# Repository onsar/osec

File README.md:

# osec
###Proyecto de para el desarrollo de un demostrador de software libre para el control de la energía

En la primera fase monitorizamos una instalación solar fotovoltaica mixta que esta compuesta por paneles fotovoltaicos y térmicos. Los tipos de sensores que incluye son:

* Intensidad en continua
* Temperatura del agua
* Caudal
* Presión del circuito hidráulico

En una segunda fases optimizaremos el circuito

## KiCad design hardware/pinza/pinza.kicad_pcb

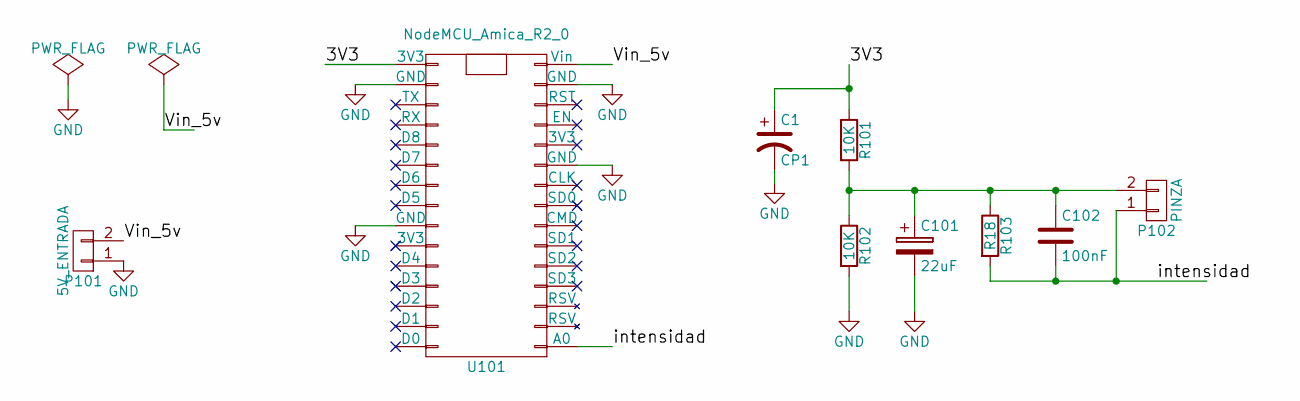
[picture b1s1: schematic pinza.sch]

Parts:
C1: CP1; C_Radial_D5_L11_P2
C101: 22uF; C_Radial_D5_L11_P2
C102: 100nF; C_Disc_D3_P2.5
P101: 5V_ENTRADA; bornier2
P102: PINZA; bornier2
R101, R102: 10K; Resistor_Horizontal_RM10mm
R103: R18; Resistor_Horizontal_RM10mm
U101: NodeMCU_Amica_R2_0; NodeMCU_Amica_R2

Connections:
/3V3: C1.1, R101.1, U101.16 (3V3)
/Vin_5v: P101.2, U101.15 (Vin)
/intensidad: C102.2, P102.1, R103.2, U101.1 (A0)
GND: C1.2, C101.2, P101.1, R102.2, U101.10 (GND), U101.14 (GND), U101.17 (GND), U101.24 (GND)
unnamed: C101.1, C102.1, P102.2, R101.2, R102.1, R103.1

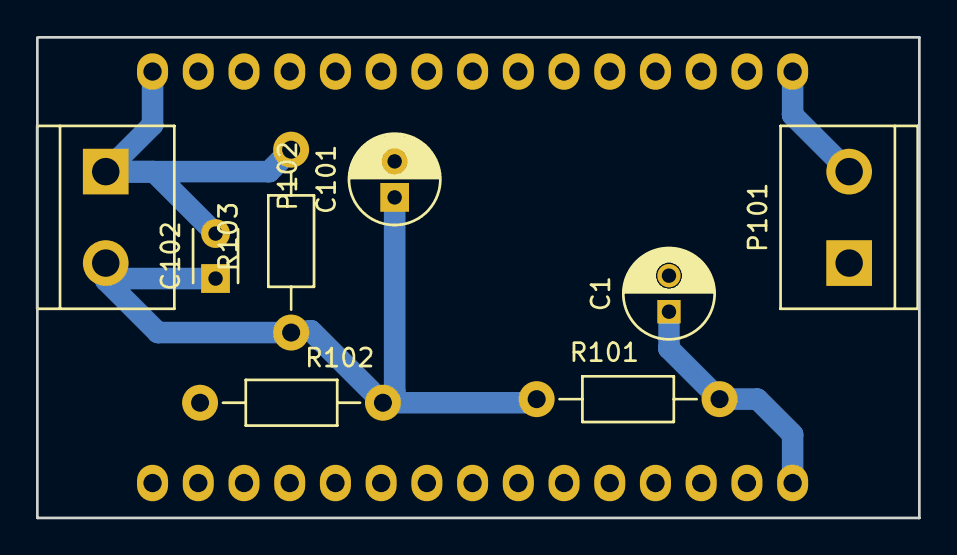
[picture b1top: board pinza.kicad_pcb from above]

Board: 2 copper layers, 49.0 x 26.7 mm, 9 parts (1 on the bottom side), 5 nets.

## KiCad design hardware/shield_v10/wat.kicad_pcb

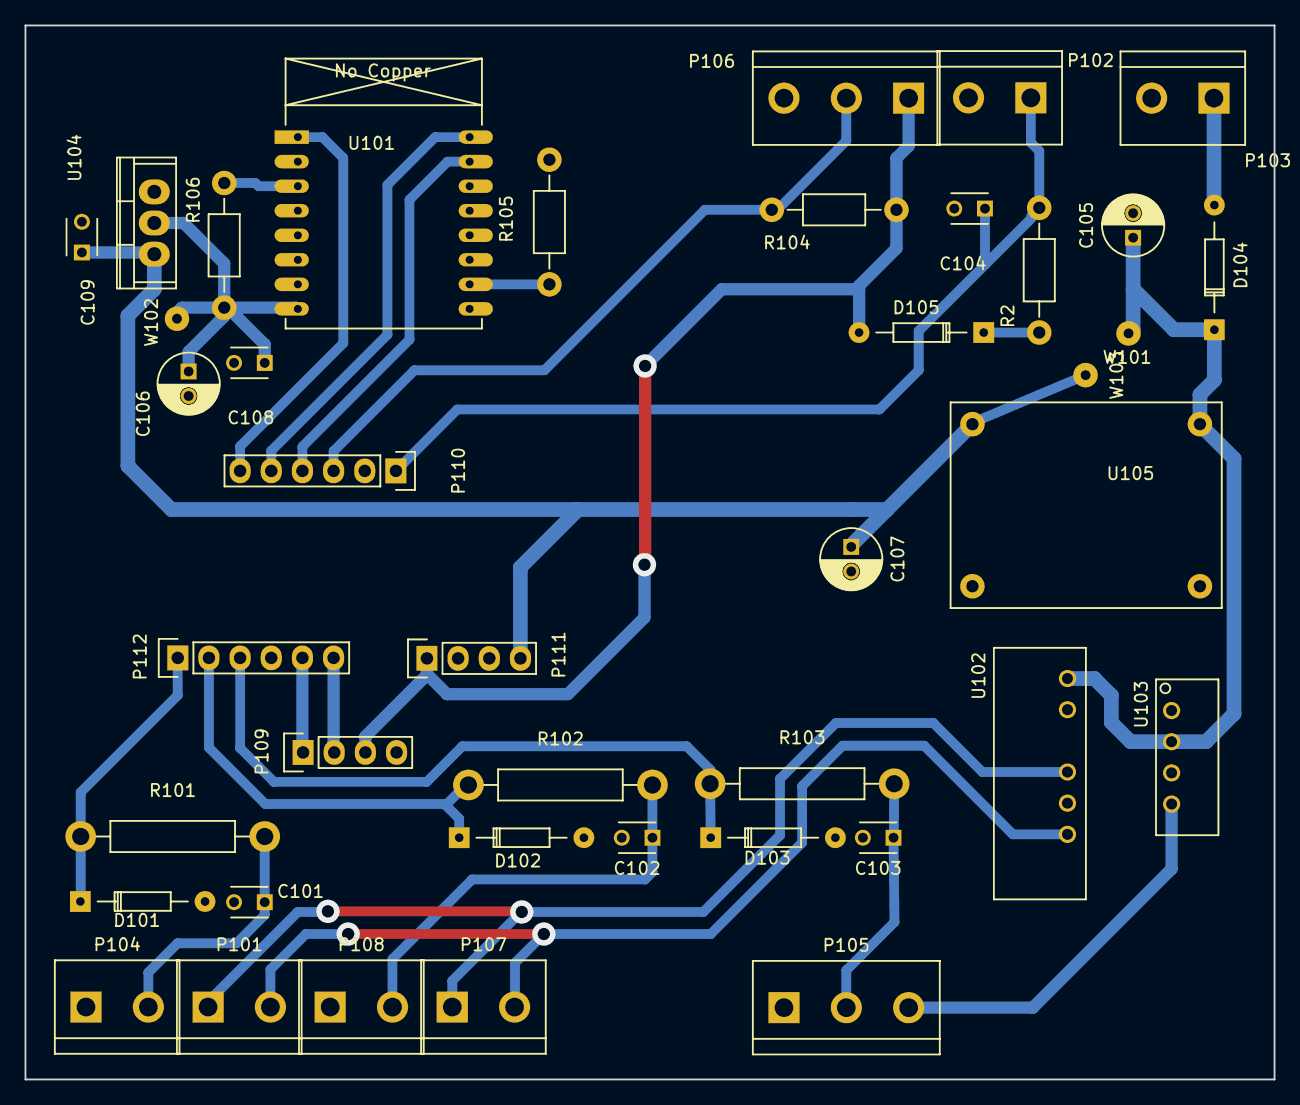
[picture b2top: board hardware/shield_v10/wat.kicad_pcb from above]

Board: 2 copper layers, 101.8 x 85.9 mm, 41 parts (0 on the bottom side), 25 nets.

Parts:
C101, C102, C103, C104, C108, C109: 100nF; C_Disc_D3_P2.5
C105: 220uF; C_Radial_D5_L11_P2
C106, C107: 22uF; C_Radial_D5_L11_P2
D101, D102, D103: ZENER; Diode_DO-35_SOD27_Horizontal_RM10
D104, D105: 1N4007; Diode_DO-35_SOD27_Horizontal_RM10
P101: INTEN_1_V; bornier2
P102: CAUDAL_1; bornier2
P103: V_IN; bornier2
P104: INTEN_1_I; bornier2
P105: PRESION_1; bornier3
P106: 18b20; bornier3
P107: INTEN_2_V; bornier2
P108: INTEN_2_I; bornier2
P109: LCD_I2C; Pin_Header_Straight_1x04
P110: ARD_DI_06; Pin_Header_Straight_1x06
P111: ARD_ALI_04; Pin_Header_Straight_1x04
P112: ARD_AN_I2C; Pin_Header_Straight_1x06
R2, R105, R106: 10K; Resistor_Horizontal_RM10mm
R101, R102, R103: 1K; Resistor_RM15mm_pad
R104: 2K; Resistor_Horizontal_RM10mm
U101: ESP-12; ESP-07v2_pad
U102: Recom-rd
U103: RO-1224S; RO-xxxxS
U104: LM1117; TO-220-LM117
U105: mp-1584; MP-1584-SD
W101: +12V; SolderWirePad_single_0-8mmDrill
W102: +3,3V; SolderWirePad_single_0-8mmDrill
W103: +8V; SolderWirePad_single_0-8mmDrill

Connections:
/18b20: P106.2, P110.3, R104.1
/+15_voltios: P101.2, P107.2, U102.6
/+24_voltios: P105.3, U103.4
/-15_voltios: P101.1, P107.1, U102.4
/Var_8V: C107.1, C109.1, P111.4, U104.VI, U105.3, W103.1
/Ves_3V3: C106.1, C108.1, R106.1, U101.8, U104.VO, W102.1
/Vin_12V: C105.1, D104.1, U102.1, U103.2, U105.2, W101.1
/Vpc_5V: D105.2, P106.1, P109.3, P111.1, R104.2
/caudal_1: C104.1, P102.1, P110.1, R2.2
/e_cpd: R106.2, U101.3
/e_g15: R105.1, U101.10
/e_rst: P110.6, U101.1
/e_rx: P110.4, U101.15
/e_tx: P110.5, U101.16
/intensidad_1: D101.1, P112.1, R101.1
/intensidad_2: D102.1, P112.2, R102.1
/presion_1: D103.1, P112.3, R103.1
/scl: P109.2, P112.6
/sda: P109.1, P112.5
GND: C101.2, C102.2, C103.2, C104.2, C105.2, C106.2, C107.2, C108.2, C109.2, D101.2, D102.2, D103.2, P102.2, P103.2, P104.1, P105.1, P106.3, P108.1, P109.4, P111.3, R105.2, U101.9, U102.2, U102.5, U103.1, U103.3, U104.GND, U105.1, U105.4
unnamed: C101.1, P104.2, R101.2
unnamed: C102.1, P108.2, R102.2
unnamed: C103.1, P105.2, R103.2
unnamed: D104.2, P103.1
unnamed: D105.1, R2.1

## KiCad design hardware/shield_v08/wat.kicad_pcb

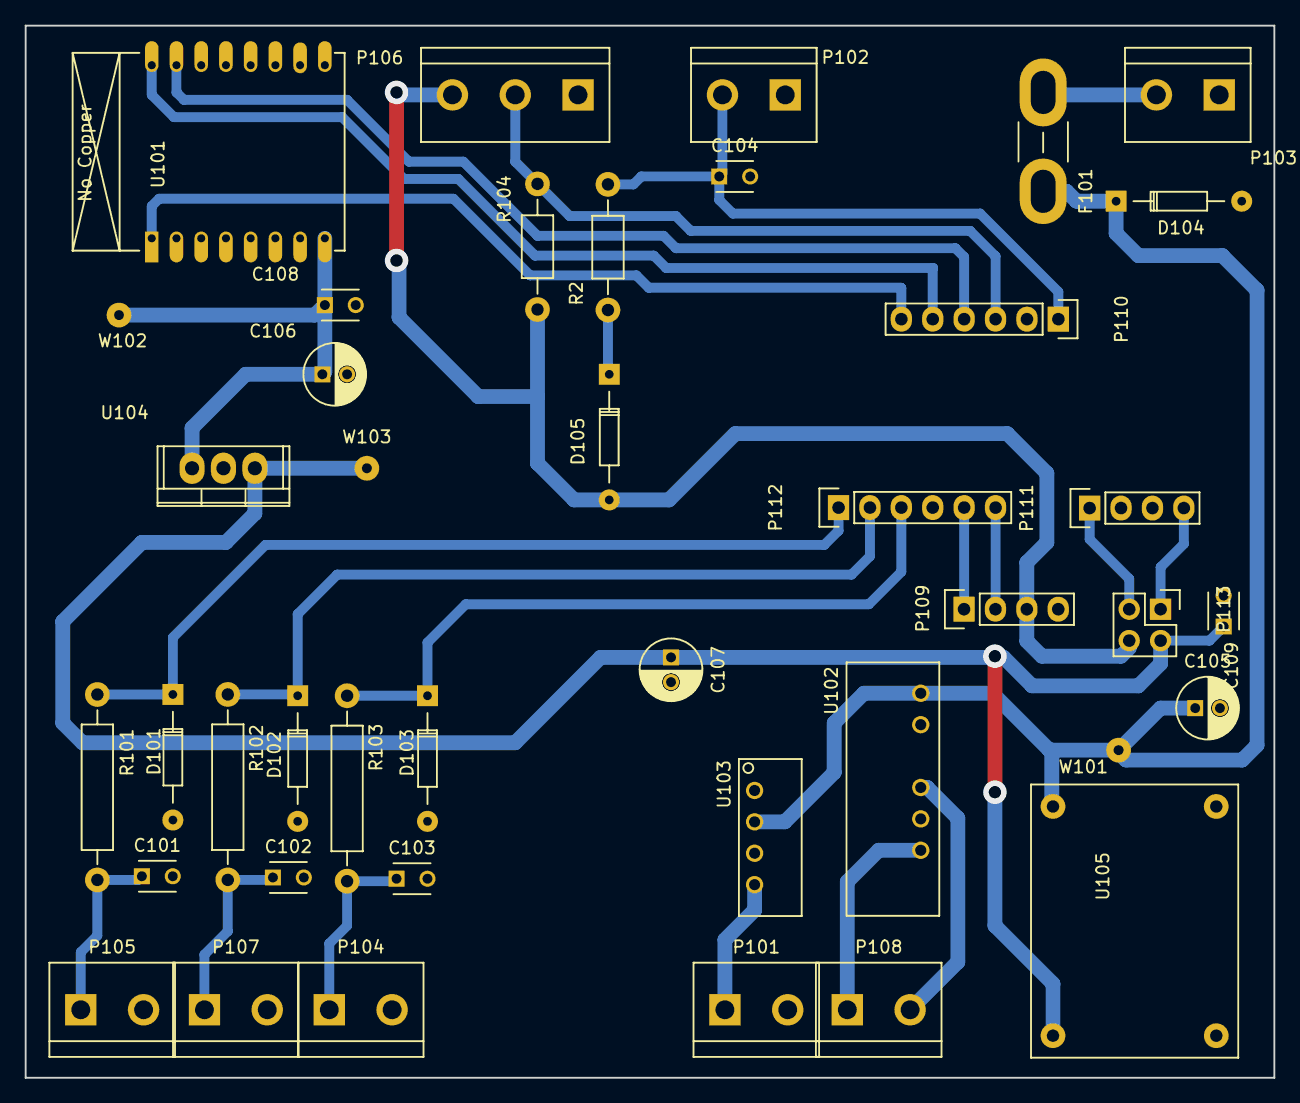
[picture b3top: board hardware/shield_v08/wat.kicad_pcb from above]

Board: 2 copper layers, 101.0 x 85.1 mm, 41 parts (0 on the bottom side), 25 nets.

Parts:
C101, C102, C103, C104, C108, C109: 100nF; C_Disc_D3_P2.5
C105: 220uF; C_Radial_D5_L11_P2
C106, C107: 22uF; C_Radial_D5_L11_P2
D101, D102, D103: ZENER; Diode_DO-35_SOD27_Horizontal_RM10
D104, D105: 1N4007; Diode_DO-35_SOD27_Horizontal_RM10
F101: Fuse; BladeFuse-Mini
P101: 24VOL; bornier2
P102: CAUDAL_1; bornier2
P103: V_IN; bornier2
P104: PRESION_1; bornier2
P105: INTENSIDAD_1; bornier2
P106: 18b20; bornier3
P107: INTENSIDAD_2; bornier2
P108: 15VOL; bornier2
P109: LCD_I2C; Pin_Header_Straight_1x04
P110: ARD_DI_06; Pin_Header_Straight_1x06
P111: ARD_ALI_04; Pin_Header_Straight_1x04
P112: ARD_AN_I2C; Pin_Header_Straight_1x06
P113: CONN_02X02; Pin_Header_Straight_2x02
R2: 10K; Resistor_Horizontal_RM10mm
R101, R102, R103: 1K; Resistor_Horizontal_RM15mm
R104: 2K; Resistor_Horizontal_RM10mm
U101: ESP-12; ESP-07v2
U102: Recom-rd
U103: RO-1224S; RO-xxxxS
U104: LM1117; TO-220
U105: mp-1584; MP-1584-SD
W101: +12V; SolderWirePad_single_0-8mmDrill
W102: +3,3V; SolderWirePad_single_0-8mmDrill
W103: +8V; SolderWirePad_single_0-8mmDrill

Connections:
/18b20: P106.2, P110.3, R104.1
/Var_8V: C107.1, C109.1, P113.2, U104.VI, U105.3, W103.1
/Ves_3V3: C106.1, C108.1, U101.8, U104.VO, W102.1
/Vin_12V: C105.1, D104.1, F101.2, U102.1, U103.2, U105.2, W101.1
/Vpc_5V: D105.2, P106.3, P109.3, P113.4, R104.2
/caudal_1: C104.1, P102.2, P110.1, R2.2
/e_rst: P110.6, U101.1
/e_rx: P110.4, U101.15
/e_tx: P110.5, U101.16
/intensidad_1: D101.1, P112.1, R101.1
/intensidad_2: D102.1, P112.2, R102.1
/presion_1: D103.1, P112.3, R103.1
/scl: P109.2, P112.6
/sda: P109.1, P112.5
GND: C101.2, C102.2, C103.2, C104.2, C105.2, C106.2, C107.2, C108.2, C109.2, D101.2, D102.2, D103.2, D104.2, P101.2, P102.1, P103.1, P104.2, P105.2, P106.1, P107.2, P109.4, P111.3, U101.9, U102.2, U102.5, U103.1, U103.3, U104.GND, U105.1, U105.4
unnamed: C101.1, P105.1, R101.2
unnamed: C102.1, P107.1, R102.2
unnamed: C103.1, P104.1, R103.2
unnamed: D105.1, R2.1
unnamed: F101.1, P103.2
unnamed: P101.1, U103.4
unnamed: P108.1, U102.6
unnamed: P108.2, U102.4
unnamed: P111.1, P113.3
unnamed: P111.4, P113.1

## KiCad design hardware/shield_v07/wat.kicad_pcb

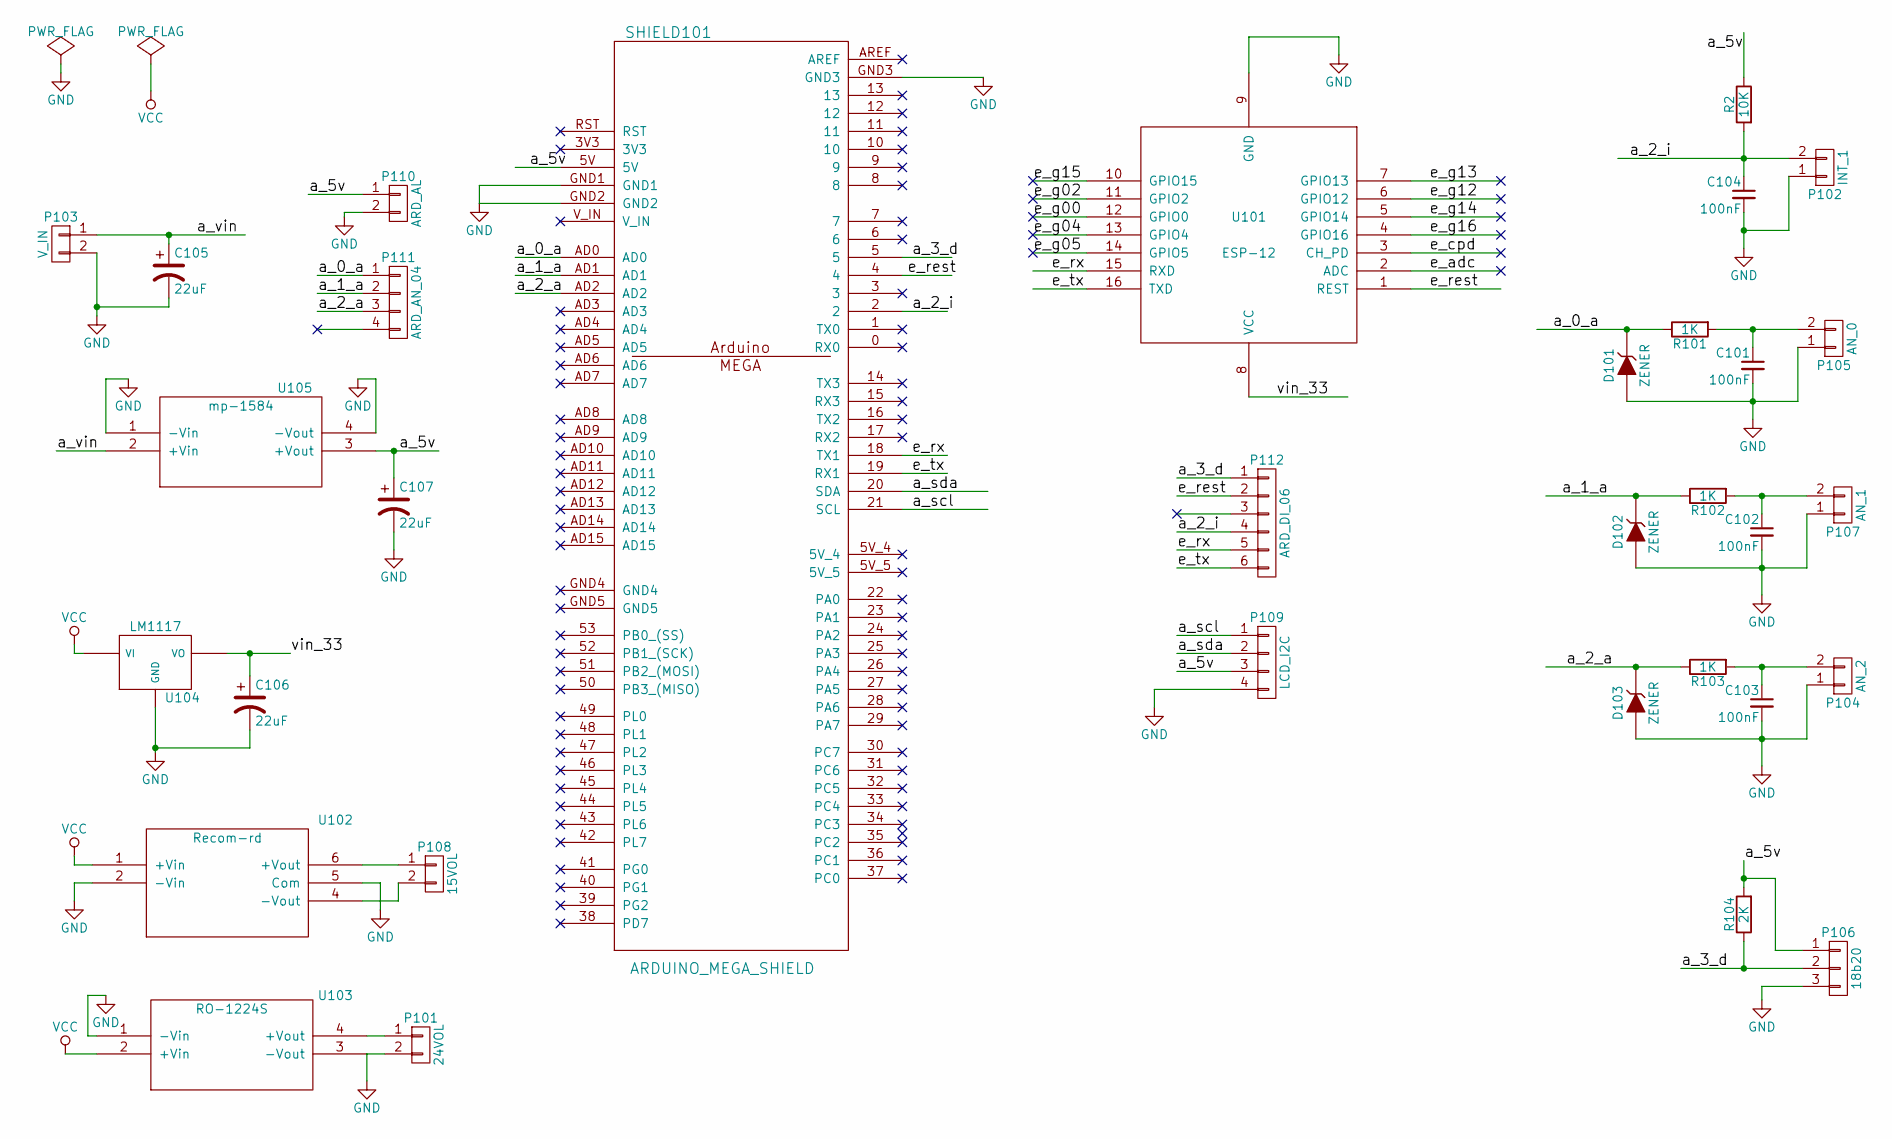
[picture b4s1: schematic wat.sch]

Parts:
C101, C102, C103, C104: 100nF; C_Disc_D3_P2.5
C105, C106, C107: 22uF; C_Radial_D5_L11_P2
D101, D102, D103: ZENER; Diode_DO-35_SOD27_Horizontal_RM10
P101: 24VOL; bornier2
P102: INT_1; bornier2
P103: V_IN; bornier2
P104: AN_2; bornier2
P105: AN_0; bornier2
P106: 18b20; bornier3
P107: AN_1; bornier2
P108: 15VOL; bornier2
P109: LCD_I2C; Pin_Header_Straight_1x04
P110: ARD_AL; Pin_Header_Straight_1x02
P111: ARD_AN_04; Pin_Header_Straight_1x04
P112: ARD_DI_06; Pin_Header_Straight_1x06
R2: 10K; Resistor_Horizontal_RM10mm
R101, R102, R103: 1K; Resistor_Horizontal_RM15mm
R104: 2K; Resistor_Horizontal_RM10mm
SHIELD101: ARDUINO_MEGA_SHIELD; ARDUINO MEGA SHIELD
U101: ESP-12; ESP-07v2
U102: Recom-rd
U103: RO-1224S; RO-xxxxS
U104: LM1117; TO-220
U105: mp-1584; MP-1584-SD

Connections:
/a_0_a: D101.1 (K), P111.1, R101.1, SHIELD101.AD0
/a_1_a: D102.1 (K), P111.2, R102.1, SHIELD101.AD1
/a_2_a: D103.1 (K), P111.3, R103.1, SHIELD101.AD2
/a_2_i: C104.1, P102.2, P112.4, R2.2, SHIELD101.2
/a_3_d: P106.2, P112.1, R104.1, SHIELD101.5
/a_5v: C107.1, P106.1, P109.3, P110.1, R2.1, R104.2, SHIELD101.5V, U105.3 (+Vout)
/a_scl: P109.1, SHIELD101.21 (SCL)
/a_sda: P109.2, SHIELD101.20 (SDA)
/a_vin: C105.1, P103.1, U105.2 (+Vin)
/e_adc: U101.2 (ADC)
/e_cpd: U101.3 (CH_PD)
/e_g00: U101.12 (GPIO0)
/e_g02: U101.11 (GPIO2)
/e_g04: U101.13 (GPIO4)
/e_g05: U101.14 (GPIO5)
/e_g12: U101.6 (GPIO12)
/e_g13: U101.7 (GPIO13)
/e_g14: U101.5 (GPIO14)
/e_g15: U101.10 (GPIO15)
/e_g16: U101.4 (GPIO16)
/e_rest: P112.2, SHIELD101.4, U101.1 (REST)
/e_rx: P112.5, SHIELD101.18 (TX1), U101.15 (RXD)
/e_tx: P112.6, SHIELD101.19 (RX1), U101.16 (TXD)
/vin_33: C106.1, U101.8 (VCC), U104.VO
GND: C101.2, C102.2, C103.2, C104.2, C105.2, C106.2, C107.2, D101.2 (A), D102.2 (A), D103.2 (A), P101.2, P102.1, P103.2, P104.1, P105.1, P106.3, P107.1, P109.4, P110.2, SHIELD101.GND1, SHIELD101.GND2, SHIELD101.GND3, U101.9 (GND), U102.2 (-Vin), U102.5 (Com), U103.1 (-Vin), U103.3 (-Vout), U104.GND, U105.1 (-Vin), U105.4 (-Vout)
unnamed: C101.1, P105.2, R101.2
unnamed: C102.1, P107.2, R102.2
unnamed: C103.1, P104.2, R103.2
unnamed: P101.1, U103.4 (+Vout)
unnamed: P108.1, U102.6 (+Vout)
unnamed: P108.2, U102.4 (-Vout)
VCC: U102.1 (+Vin), U103.2 (+Vin), U104.VI

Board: 2 copper layers, 33 parts (1 on the bottom side), 21 nets, no tracks yet.

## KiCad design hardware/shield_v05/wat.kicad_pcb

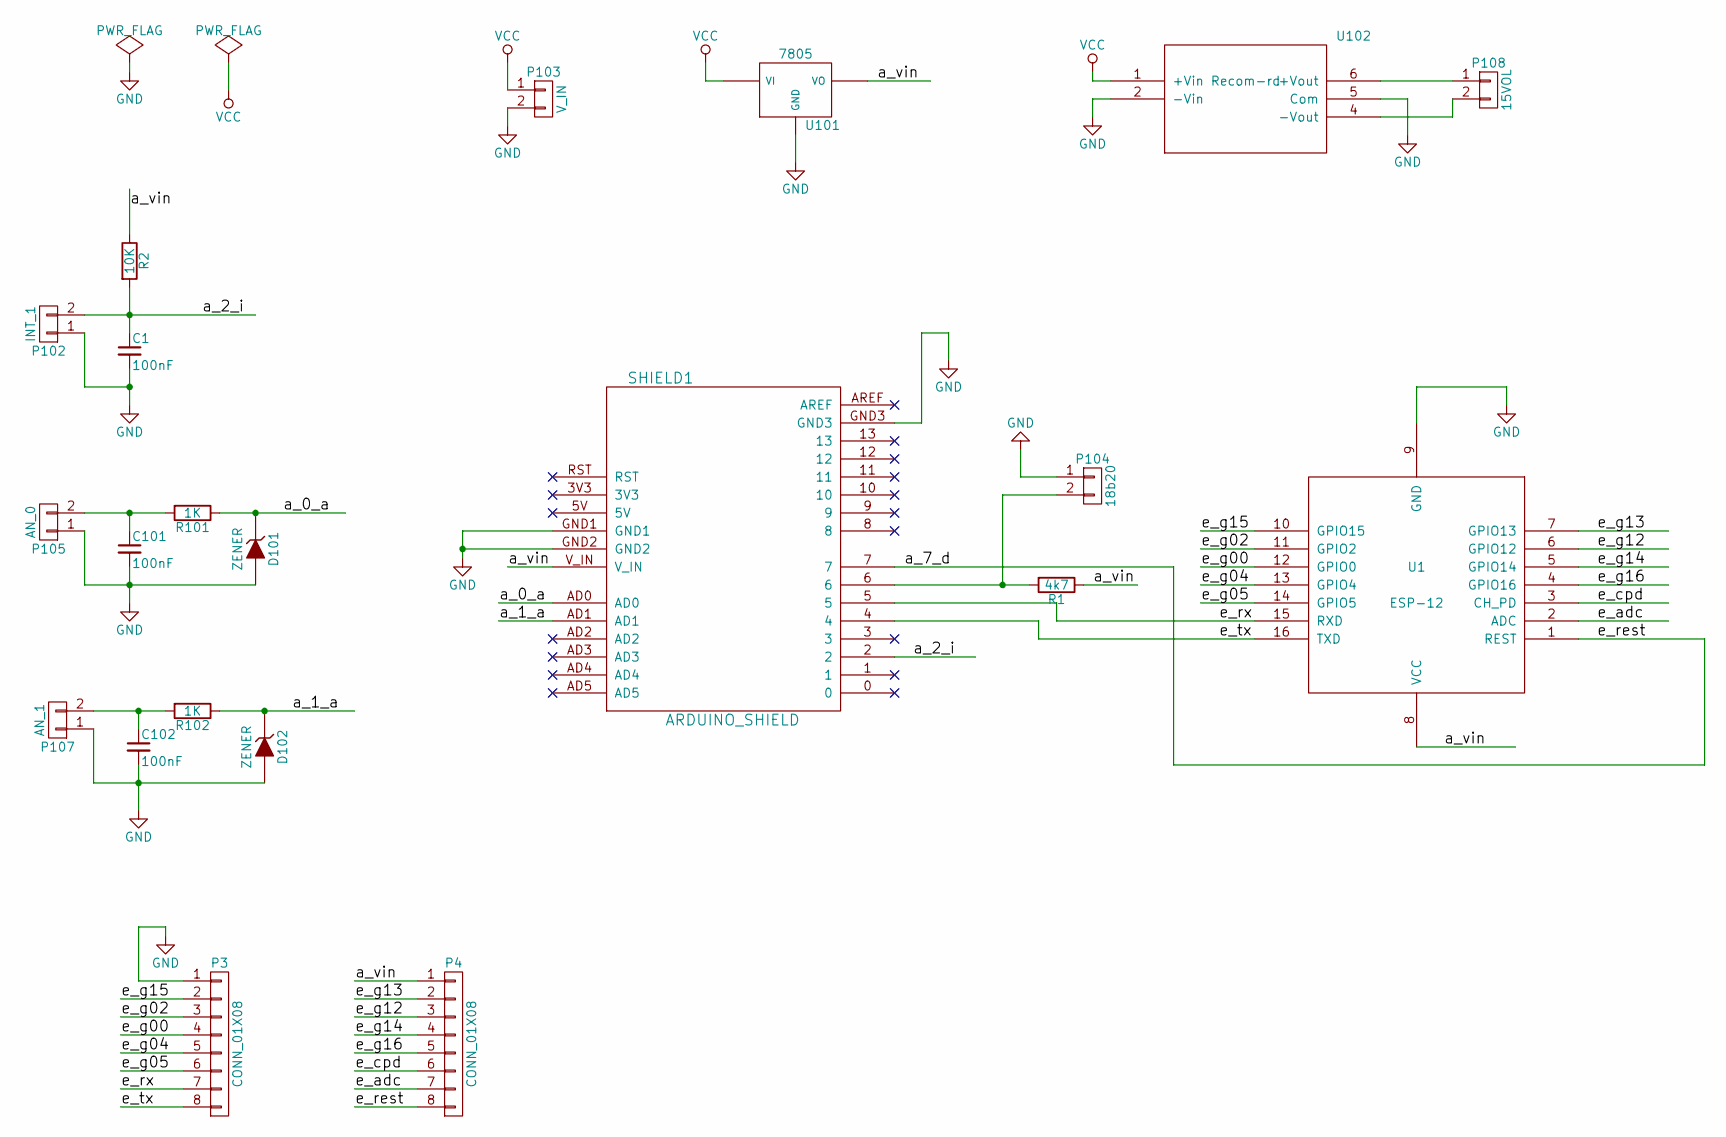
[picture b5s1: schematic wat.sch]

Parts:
C1, C101, C102: 100nF; C_Disc_D3_P2.5
D101, D102: ZENER; Diode_DO-35_SOD27_Horizontal_RM10
P3, P4: CONN_01X08; Pin_Header_Straight_1x08
P102: INT_1; bornier2
P103: V_IN; bornier2
P104: 18b20; bornier2
P105: AN_0; bornier2
P107: AN_1; bornier2
P108: 15VOL; bornier2
R1: 4k7; Resistor_Horizontal_RM10mm
R2: 10K; Resistor_Horizontal_RM10mm
R101, R102: 1K; Resistor_Horizontal_RM10mm
SHIELD1: ARDUINO_SHIELD; ARDUINO SHIELD
U1: ESP-12
U101: 7805; TO-220
U102: Recom-rd

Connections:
/a_0_a: D101.1 (K), R101.1, SHIELD1.AD0
/a_1_a: D102.1 (K), R102.1, SHIELD1.AD1
/a_2_i: C1.1, P102.2, R2.2, SHIELD1.2
/a_7_d: P4.8, SHIELD1.7, U1.1 (REST)
/a_vin: P4.1, R1.1, R2.1, SHIELD1.V_IN, U1.8 (VCC), U101.VO
/e_adc: P4.7, U1.2 (ADC)
/e_cpd: P4.6, U1.3 (CH_PD)
/e_g00: P3.4, U1.12 (GPIO0)
/e_g02: P3.3, U1.11 (GPIO2)
/e_g04: P3.5, U1.13 (GPIO4)
/e_g05: P3.6, U1.14 (GPIO5)
/e_g12: P4.3, U1.6 (GPIO12)
/e_g13: P4.2, U1.7 (GPIO13)
/e_g14: P4.4, U1.5 (GPIO14)
/e_g15: P3.2, U1.10 (GPIO15)
/e_g16: P4.5, U1.4 (GPIO16)
/e_rx: P3.7, SHIELD1.5, U1.15 (RXD)
/e_tx: P3.8, SHIELD1.4, U1.16 (TXD)
GND: C1.2, C101.2, C102.2, D101.2 (A), D102.2 (A), P3.1, P102.1, P103.2, P104.1, P105.1, P107.1, SHIELD1.GND1, SHIELD1.GND2, SHIELD1.GND3, U1.9 (GND), U101.GND, U102.2 (-Vin), U102.5 (Com)
unnamed: C101.1, P105.2, R101.2
unnamed: C102.1, P107.2, R102.2
unnamed: P104.2, R1.2, SHIELD1.6
unnamed: P108.1, U102.6 (+Vout)
unnamed: P108.2, U102.4 (-Vout)
VCC: P103.1, U101.VI, U102.1 (+Vin)

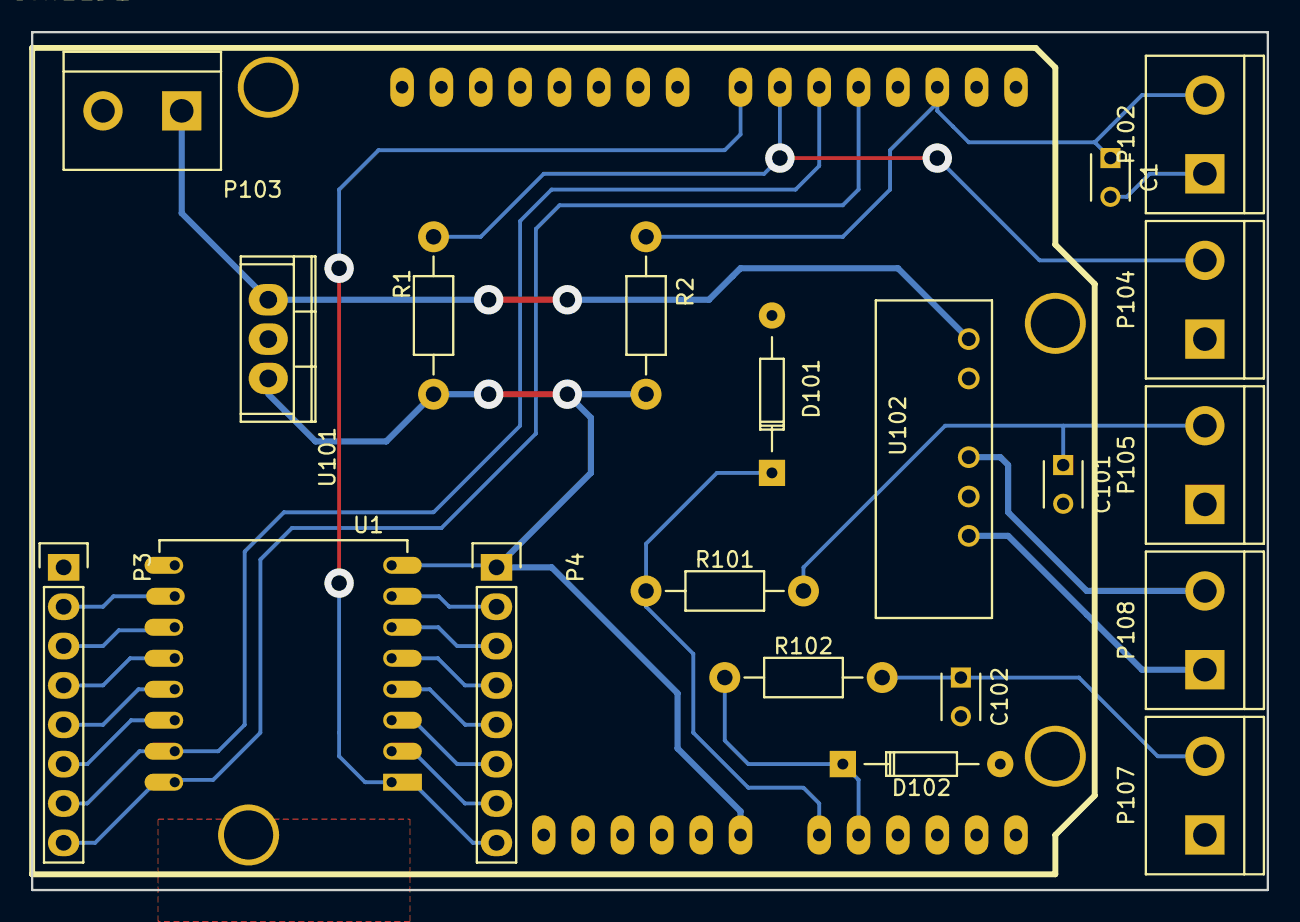
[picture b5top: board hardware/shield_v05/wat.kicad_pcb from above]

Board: 2 copper layers, 79.8 x 55.4 mm, 21 parts (0 on the bottom side), 25 nets.

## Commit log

2016-10-20 2016-10-19 Acta de reunión del grupo de desarrollo
2016-10-20 borrador de requisitos del demostrador
2016-11-02 [arduino]primera versión sensor temperatura
2016-11-02 cambio de directorio
2016-11-02 nuevo directorio arduino
2016-11-02 comentario
2016-11-03 [arduino]busqueda sensores de temperatura
2016-11-03 [arduino]autodetecta, comprueba alarmas, lee temperatura
2016-11-04 [arduino]incluse asignacion de nombres a los sensores
2016-11-07 Pandora Pakages
2016-11-08 [arduino]mesnajes json, borrar alarma temeperatura
2016-11-08 [arduino]ejemplos json
2016-11-16 [arduino]sensor de presion
2016-11-17 sensor de medida de caudal
2016-11-21 [documentacion] circuito para probar LEN HAS 100S
2016-11-22 [arduino]sensor de intensidad len-has-100s
2016-12-01 [arduino]modulo de prueba de wifi
2016-12-02 [arduino]limpieza codigo wifi
2016-12-06 [arduino]sensor de temperatura por wifi
2016-12-06 [herramientas]cliente para leer de un puerto
2016-12-07 [herramientas] nueva version para leer mensajes
2016-12-08 [herramientas]read_msj con log
2016-12-08 [herramientas]correccion menor en scrpt
2016-12-08 [herramientas]actualización de herramientas
2016-12-08 [herramientas]simulador en servidor
2016-12-09 [herramientas]nuevo simulador
2016-12-09 [herramientas]cambios en el simulador
2016-12-15 [arduino]cambio de pines asignados
2016-12-21 [arduino]cambios de configuración
2016-12-21 [scripts]cinfiguracion
2016-12-21 [arduino]borrar libreria keypad
2016-12-26 [arduino]post+at_basico+uwsgi
2016-12-28 [arduino] ESP 8266 con comandos basicos
2016-12-29 [arduino]mejoras conexion wifi
2017-01-03 [arduino] wifi operativa contra servidor
2017-01-03 [uwsgi] script de pare recibir post de temperatura
2017-01-03 cambio menor
2017-01-03 cambio menor_1
2017-01-11 [arduino]añadidos sensores analógicos + println(F
2017-01-12 [arduino]medidor de caudal por interrupciones
2017-02-01 [arduino]incluidos cambios tipfd_wifi
2017-02-01 [arduino] modificaciones para la pantalla
2017-02-01 [arduino cambio de nombres]
2017-02-08 [hardware]primera version hardware
2017-02-08 [hardware] borro ficheros gerber
2017-02-09 [hardware] borrador esquema alimentacion
2017-02-10 [arduino][hardware]midificacion one wire, libreria nuevos componentes
2017-02-18 [arduino]pcb para carril din
2017-02-20 Esquema modificado domingo noche
    cambios
2017-02-20 [pcb]mejoras version 3
2017-02-20 [pcb]repongo librerias de huellas
2017-02-21 [pdb] cambio posicion nano
2017-02-24 [pcb]avance version 3
2017-02-25 [pcb]version 3 completa
2017-03-04 [pcb]herramientas actualizar fw del ESP
2017-03-06 [arduino]version para nano
2017-03-15 Estado actual
2017-03-26 [server]creacion de site()agente por mensaje post
2017-03-28 [arduino]incluyo instalacion endef
2017-04-15 [web]initial commit
2017-04-15 menor
2017-04-19 [arduino]actualizar codigo Endef
2017-04-19 [nodemcu]primer codigo de pruebas
2017-04-19 [hardware]borrar informacion obsoleta
2017-04-25 [nodemcu]primeras pruebas
2017-04-29 [nodemcu]tx 18b20 por wifi
2017-05-03 [arduino] ultimos cambios para hotel hacienda
2017-05-03 [nodemcu]modificaciones libreria emon
2017-05-06 [arduino]codigos 18b20 instalacion hacienda
2017-05-11 [nodemcu]basico para medida de intensidad
2017-05-15 [pcb]version 10
2017-05-15 [pcb] beta de la pcb
2017-05-15 [pcb] mejoras menores
2017-05-31 [hardware]v10 y pinza
2017-05-31 [nodemcu medida de intensidad]
2017-06-03 [nodemcu]irms y wifi
2017-06-05 [menos]cambio menor
2017-06-17 [pcb]version_11 pinzas de consumo
2017-07-16 [nodemcu]pruebas bajar a cerpo la Irms
2017-07-16 [hardware]pinza nodemcu
2017-07-16 [EmonESP]software y librerias -> ok
2017-07-16 [nodemcu]pruebas
2017-07-16 [EmonESP]tools -> ok_1
2017-07-16 [nodemcu]fichero de wifi
2017-08-29 [ESP] cambios menores
2017-09-04 cambio firmware ESP
2018-04-06 añado documentacion
2018-04-06 primera correccion de oscar
